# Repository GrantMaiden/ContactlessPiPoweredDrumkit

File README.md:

#  (byte)this.beat  
Welcome to the github landing page for the first prototype of the **(byte)this.beat** drumkit!

(byte)this.beat is an innovative, contactless, raspberry pi-powered drumkit being developed for  Real Time Embedded Programming (ENG5220) at the University of Glasgow.  The contactless drumkit aims to be a simple, easy-to-use interface that accommodates entry level users---being a introductory device to jam out on---as well as a device for professional musicians, conforming to sub 20ms latency requirements and high quality, 48000khz drum samples.

Please download the latest release to access the most recent stable version of the source code. Keep in mind that hardware is required to run this project!

## So what's the tempo?

* The challenge set for this course was to develop any real time embedded project, using a Raspberry Pi 3 and a £45 budget.  
* Selecting an appropriate sensor that can be used in a real-time system that is affordable, has a high sample rate, and great data resolution was challenging. After a thorough amount of market research, the [VL53L4CD](https://www.st.com/en/imaging-and-photonics-solutions/vl53l4cd.html) ranging sensor was selected as the most suitable ic for our project. Turning them into "invisible" drum modules so that you can jam out in thin air seemed a perfect task!  
* The distance values measured by the sensors every 10ms are used to calculate the velocity of any objects directly above the sensors. A detection algorithm is derived by being a combination of when the velocity changes direction, and what the previous 80ms of velocity was measured as. Thus, it is possible to use the sensor data to not only detect when a drum hit has been detected, but also at what intensity!

## Team Collaboration and Project Management

Project management was done by utilising a teams channel for collaboration. At the start of our group project, keeping in mind an agile team development environment, a Gantt chart was created in excel and hosted on our teams channel. Our team had two meetings each week throughout the semester; the first of which was primarily for project planning and updates, and the second meeting was for development and one-on-one problem solving, if necessary. Github issues were utilised as a means to give feedback as our project development continued. All Project Discussions, meeting notes, and development feasibility studies can be found at our [sharepoint](https://gla.sharepoint.com/:o:/s/ENG5228RTEP/Er4JzmCRMUZCnUjhNUSQIA8BrX5IVSQI6c456dHyLfZf0w?e=HDqj4z).  
This link is accessible by anyone with a University of Glasgow account. 
GitHub issues were used as a way to track the development of the project. The issues can be viewed from the header of this page, above the directory browser.

## Project Setup and Initialisation
### Hardware Requirements
* Assembled (byte)this.beat board
* Raspberry Pi updated with latest Raspbian image
* Speaker attached to Audio Jack
### Software Setup
* Complete project setup instructions located in the [Embedded Directory](https://github.com/GrantMaiden/ContactlessPiPoweredDrumkit/tree/main/embedded) on your local raspberry pi
* Download the latest release of the firmware, and compile the source code in the embedded directory by following the [cmake build instructions](https://github.com/GrantMaiden/ContactlessPiPoweredDrumkit/blob/main/embedded/cmake_build_instructions.txt)

After running the program, an intro LED pattern will play for roughly 5 seconds, which when complete the drumkit will be able to receive ranging data. To enable sound, swipe across all 4 upwards facing sensors. The same swipe can be used to disable sound if playing needs to be paused.

## Documentation
Our code has been updated with comments that are compatible with DoxyGen, which is a great tool to generate large amounts of sufficiently segmented documentation. To view the generated documentation, first grab the latest release, then open the index.html page located in the [embedded/docs](https://github.com/GrantMaiden/ContactlessPiPoweredDrumkit/tree/main/embedded/docs) directory. In addition to the DoxyGen resource, the source code is litered with verbose explanaitons and function headers, so keep that in mind if you are modifying the source.

## Hardware Development
In order to minimise costs associated with the (byte)this.beat project, a custom Hardware design was developed. After a cost analysis completed at the beginning of the project timeline, it was concluded that designing a custom solution, rather than purchasing independent breakout boards, would allow our contactless drumkit to have a larger scope. Thus accommodating more sensors/functionality by more easily staying within our £45 budget. The discussions pertaining to analysis and cost can be seen at our [onenote](https://gla.sharepoint.com/:o:/s/ENG5228RTEP/Er4JzmCRMUZCnUjhNUSQIA8BrX5IVSQI6c456dHyLfZf0w?e=HDqj4z).  

As always, the goal with any project is to learn as much as possible while designing, thus we decided to use this opportunity to get familiar with KiCad for schematic entry. A prototype design was completed early into the semester, giving our team plenty of tolerance on receiving the fabricated boards. The fabricated board can also easily accommodate many more traces and connections than a breadboard solution could, allowing for the design scope to increase. The schematic can be seen [here](https://github.com/GrantMaiden/ContactlessPiPoweredDrumkit/blob/main/hardware/ContactlessPiPoweredDrumkit/Schematic/byteThisBeatREVA.pdf).

The drumkit had a portion of the budget left over after the primary sensor selection, so we decided to use the rest of the funds on purchasing LEDs that would aid in giving the drummer feedback during hit detection. As seen in the block diagram below, the raspberry pi communicates with 6 distance sensors, outputs to the on-board audio jack, and outputs serialised data to the LEDs.

The LEDs that were chosen are the same type of addressable LEDs that can be found on LED strips. They are affordable, and plenty of options are available. A few design challenges had to be faced regarding the decision to use these leds, however. The LEDs use 5V logic for communication, so a level shifter had to be added to translate the rpi's 3.3V logic to 5V. Secondly, the LEDs use a strict 800khz transmission rate for each bit. Serialised bits need to be given to the LEDs over a single trace, essentially the LEDs act as specialised shift registers, only forwarding their to each succeeding LED after 24bits of data has been received. The data sheet for the LEDs, along with more information regarding the protocol, can be found [here](https://github.com/GrantMaiden/ContactlessPiPoweredDrumkit/blob/main/docs/datasheets/IN-PI55TAT(X)R(X)G(X)B_v1.5.pdf). 

Due to the strict timing requirement of the LEDs, we had to use a hardware bus to send the LED bitstream, given that bitbanging at 800khz would not be consistent, and would cause too much overhead. Initially, the PCB was designed to use the uart interface for driving the LEDs, but after getting the boards in-hand and beginning development, it was found that the uart bus could not support the baudrate required (800khz*(8bits + 1stopbit) = 7.2mhz), a hardware rework was completed to change the LED control over to the SPI bus, which could accommodate the necessary frequency. The rework instructions can be found in the hardware directory.

For more information regarding the manufacturing of the (byte)this.beat board, please refer to the [hardware directory](https://github.com/GrantMaiden/ContactlessPiPoweredDrumkit/tree/main/hardware/ContactlessPiPoweredDrumkit), which includes a BOM for manufacture. The board file can also be seen in this directory. Layout was completed using KiCad, with a two-layer PCB being designed. After meeting with the EE technicians at the University of Glasgow, we found that they were unable to fabricate our design, so an overseas location was chosen for fab and assembly.

## Software 

The embedded code, being the main focus of our project, was approached with several goals for implementation:
* Real Time Coding - code is event driven and utilises hardware inputs or timers to strictly control code behavior
* Event Handling - real time events are coded with clearly defined callbacks and other async operations
* Class Encapsulation - code is written within separate classes that have clear responsibilities, obey the Liskov Substitution Principle, and are segregated, with dependency inversion
* Documentation - Verbose function headers and additional documentation generated with Doxygen to supply the user information
* Header File Constants - many constants included to aid in program control and easily modify behavior

Below, please see a diagram regarding how the major classes interact with each other within our application.

The controller class is initialised by the Main function, which on program boot creates the initial controller class. When the controller class is initialised, it will bring up the other portions of the program, which configures any necessary peripherals, and performs the bring-up procedure of the ranging sensors. This initialisation also configures asynchronous processes that use callback processes to create real-time operation of our system. The LED class uses a timer, and updates all LEDs every 2.5ms. The VL53L4CD class leaves an abstract function that is defined within the Controller class. When a hardware interrupt occurs, the VL53L4CD class will enact a callback via the virtual function.

### Bus Protocols
I2C was used as the communication protocol for each sensor. All sensors share the same bus, but are initialised with the same address. An initialization procedure had to be crafted to disable all sensors on program start, then bring-up each sensor sequentially, reprogramming the I2C bus address for the sensor, and configuring it for our high sample rate requirements.

Note: From VL53L4CD Datasheet

The SPI protocol uses custom bitshift operations to drive 6*24bits of RGB data to our addressable LEDs. The GPIO controller class handles the sending of the SPI data.
### Digital Signal Processing
The outgoing data from the ranging sensors is inherently quite noisy, and lots of artifacts exist especially once you begin to interact with them. In order to have reliable air drumming behavior, it was necessary to come up with multiple algorithms that filter the data in various ways. Keeping in mind the real-time requirements of our system, a lengthy finite reponse filter could not be used due to adding to much delay to the total system overhead. To minimise response delays, filtering was controlled using the following methods, configurable inside the controller.h header file:
* HIT_DETECT_NOISE_CHECKING   -- Enable Noise Checking/Filtering
* HIT_DETECT_NUM_SAMPLES_MIN   -- Minimum number of samples necessary for detection
* DRUM_INTERVAL_TIMEOUT_MS  -- Timeout between detection events. Caps maximum drum rate per drum
* HIT_DETECT_INSTANEOUS_VELOCITY_LIMIT  --  Velocity artificats occur frequently. If one of the detection samples' velocity is above this limit, then the drum detect is cancelled
* HIT_DETECT_AVG_VELOCITY_CEILING -- An average velocity is taken of all previous detection samples. If this average is above this threshold, then the drum detect event is negated
* HIT_DETECT_MIN_SEQUENTIAL_VELOCITY_SAMPLES  --  Minimum number of previous velocity samples below the HIT_DETECT_AVG_VELOCITY_CEILING required for a hit detect

Whenever a sensor receives data, via a virtual callback the data is sent to the controller class for processing. The controller class will take the most recent data, store the last 16 distance values into an array, and calculate the most recent velocity by taking the last sample minus the most recent sample. When the velocity calculation occurs, the velocity data is ran through a simple running average filter, via the calculation: averageVelocity = averageVelocity + (recentVelocity - averageVelocity) / VELOCITY_FACTOR_AVG. The VELOCITY_FACTOR_AVG is a constant modifiable in the controller.h header file.
A running average filter allows for a single sample overhead during averaging, and converges completely to the real average within the VELOCITY_FACTOR_AVERAGE number of samples.
As a brief example of the challenges seen during data collection and processing, refer to the below image. This image shows the Average Velocity, Recent Velocity, and current distance of each sample, in 10ms increments. 
 
## Phone Application
 
Originally, ambitious project planning had our team plan on utilising a phone application to interact with the physical drumkit, using bluetooth to handshake, modify drumkit selections, and use the phone as a speaker. We did have the opportunity to develop a prototype phone app early on in the semester. However, due to team bandwidth limitations, we were unable to see the bluetooth connectivity and phone app through to completion. 
 
It should be noted that we also discovered though substantial literature review that bluetooth bandwidth is relatively inconsistent, and even the bluetooth low latency has minimum latency intervals of about 70ms. We concluded that using bluetooth as a realtime interface would be a nightmare, and it would be best to at least keep to a physical connection regarding the sound output. We still think that a phone app would be a great way to interact with the drumkit settings, volume, etc., any we plan to continue to consider implementing one in the future.

## Unit Testing Framework
A custom unit testing framework was designed to accommodate the needs of our team collaborative efforts. When the application launches, the first code that is ran is a search to see if any input arguments are supplied. The input arguments are the inputs to our custom unit testing framework; it was deemed necessary to have a more advanced testing methodology in place as the many different blocks of our project required separate entry points depending on use case. In example, a unit test was designed to benchmark and initialise the LEDs. After the unit test was completed, the functions designed during test were integrated into the rest of the project. This design methodology was enacted in all facets of our software development. 

A list of all unit tests, their associated functions, and more specific usage instructions can be found [here](https://github.com/GrantMaiden/ContactlessPiPoweredDrumkit/blob/main/embedded/unit_tests.txt).

## Challenges and Future Improvements
Development using the raspberry pi proved to be full of challenges. Some of our team has had extensive experience with varying microcontrollers as a professional embedded engineer, and they concluded that the lack of substantial official documentation greatly complicated development. 
Here is a list of (just a few!) of the notable challenges that arose during development:
* Audio permissions -- The pigpio library requires sudo permissions, however the asla audio driver is not configured correctly to run under super user. The solution was challenging to discover, but is highlighted in the markup in our embedded directory.
* SPI bus frequency -- The embedded core clock used by the PI is not consistent. Our addressable LEDs requires fixed timing to work correctly, however the SPI clock is affected by other bus activity, USB traffic, and high load wifi connections. Essenstially, the LEDs will flicker or flash random colors when the SPI frequency deviates. As far as we know, there is no solution to this problem, but it shows that the raspberry pi is full of undocumented surprises, and is not capable of specific timing control under some circumstances.
* Some low level c libraries such as pigpio have functions to modify embedded bus behaviour, but really these values are controlled by the us and it is necessary to modify the /boot/firmware/config.txt to change things such as the I2C clock speed.
* The SPI cs gpio's can not be used as GPIO's during spi, even if SPI0 is being used, and SPI1 CS is trying to be configured as an input, even when all documentation says otherwise. This required a rework!

Some future improvements for the drumkit are planned for the next revision of the project.

* Move away from the high power, large raspberry pi to a smaller mcu. Originally one of the goals of our project was to make a device small and portable; a criteria that our device doesn't quite meet.
* Implement bluetooth communication that will interact with a peripheral phone app for control and feedback.
* Respin the board to correct hardware reworks required to accomodate SPI CS GPIO bottlenecking, and switching to the SPI from UART for LED control.
* Improve hit detection by exploring other filtering methods, and perhaps different sensors.

## Authors

* Grant Maiden  
* Peter O'Hanlon  
* Ethan Travers  
* Lucas Zehner

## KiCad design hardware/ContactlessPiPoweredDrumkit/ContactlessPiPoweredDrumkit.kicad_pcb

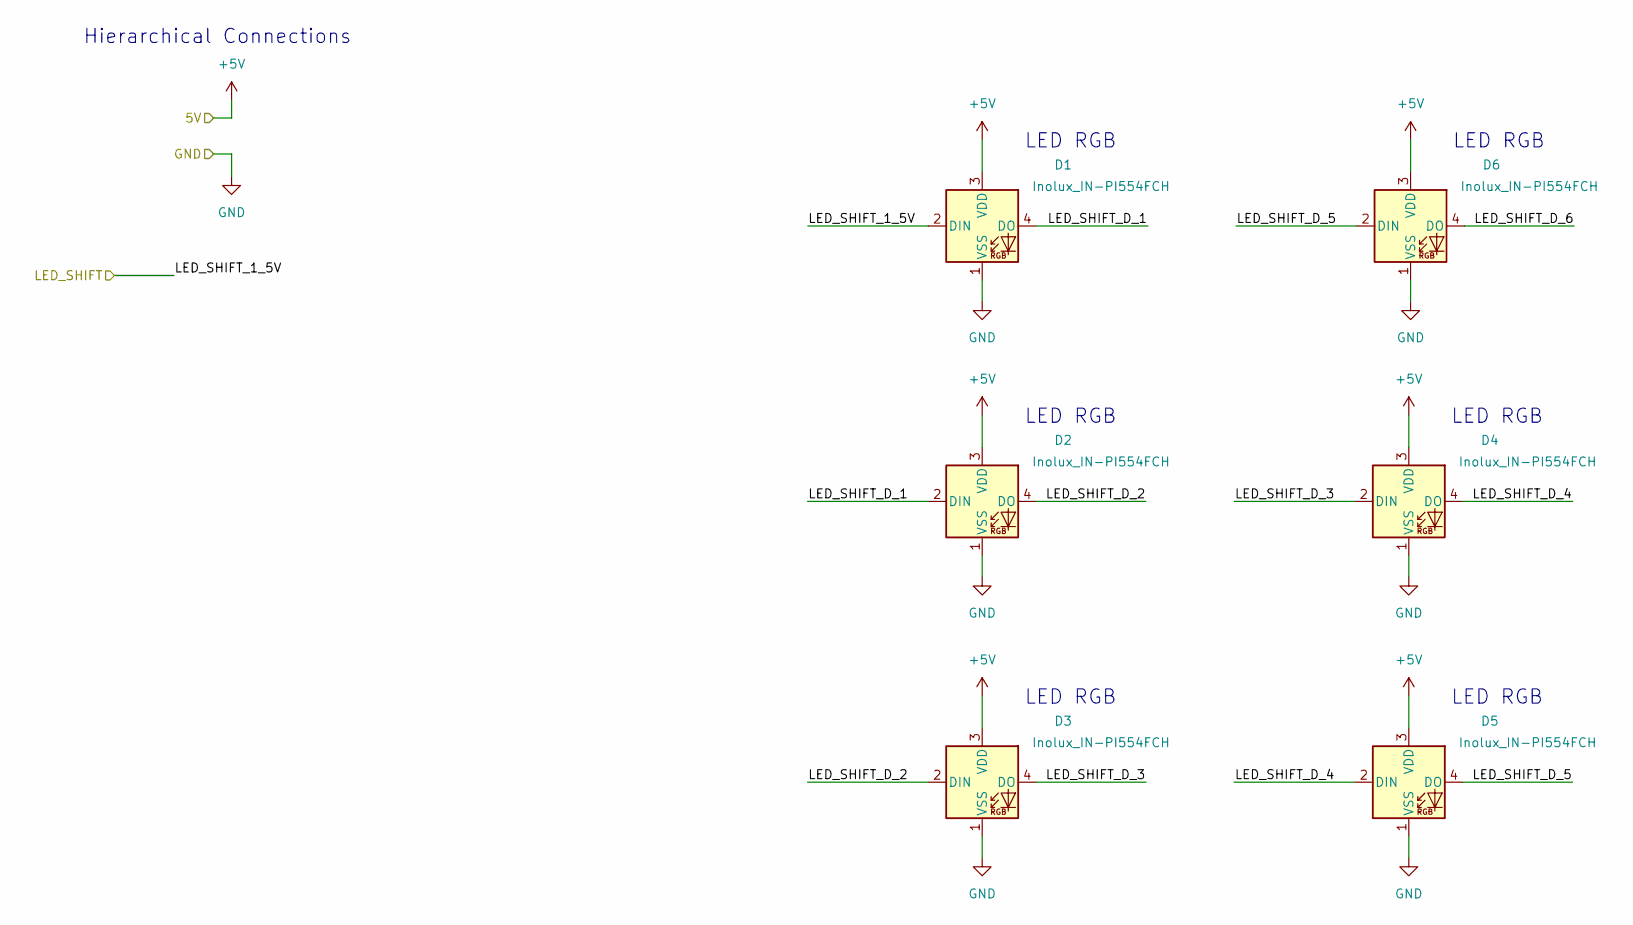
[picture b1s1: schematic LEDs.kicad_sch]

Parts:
D1, D2, D3, D4, D5, D6: Inolux_IN-PI554FCH; LED_Inolux_IN-PI554FCH_PLCC4_5.0x5.0mm_P3.2mm

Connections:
+5V: D1.3 (VDD), D2.3 (VDD), D3.3 (VDD), D4.3 (VDD), D5.3 (VDD), D6.3 (VDD); also elsewhere on the board
/LEDs/LED_SHIFT_1_5V: D1.2 (DIN); also elsewhere on the board
/LEDs/LED_SHIFT_D_1: D1.4 (DO), D2.2 (DIN)
/LEDs/LED_SHIFT_D_2: D2.4 (DO), D3.2 (DIN)
/LEDs/LED_SHIFT_D_3: D3.4 (DO), D4.2 (DIN)
/LEDs/LED_SHIFT_D_4: D4.4 (DO), D5.2 (DIN)
/LEDs/LED_SHIFT_D_5: D5.4 (DO), D6.2 (DIN)
/LEDs/LED_SHIFT_D_6: D6.4 (DO)
GND: D1.1 (VSS), D2.1 (VSS), D3.1 (VSS), D4.1 (VSS), D5.1 (VSS), D6.1 (VSS); also elsewhere on the board

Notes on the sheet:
LED RGB
Hierarchical Connections

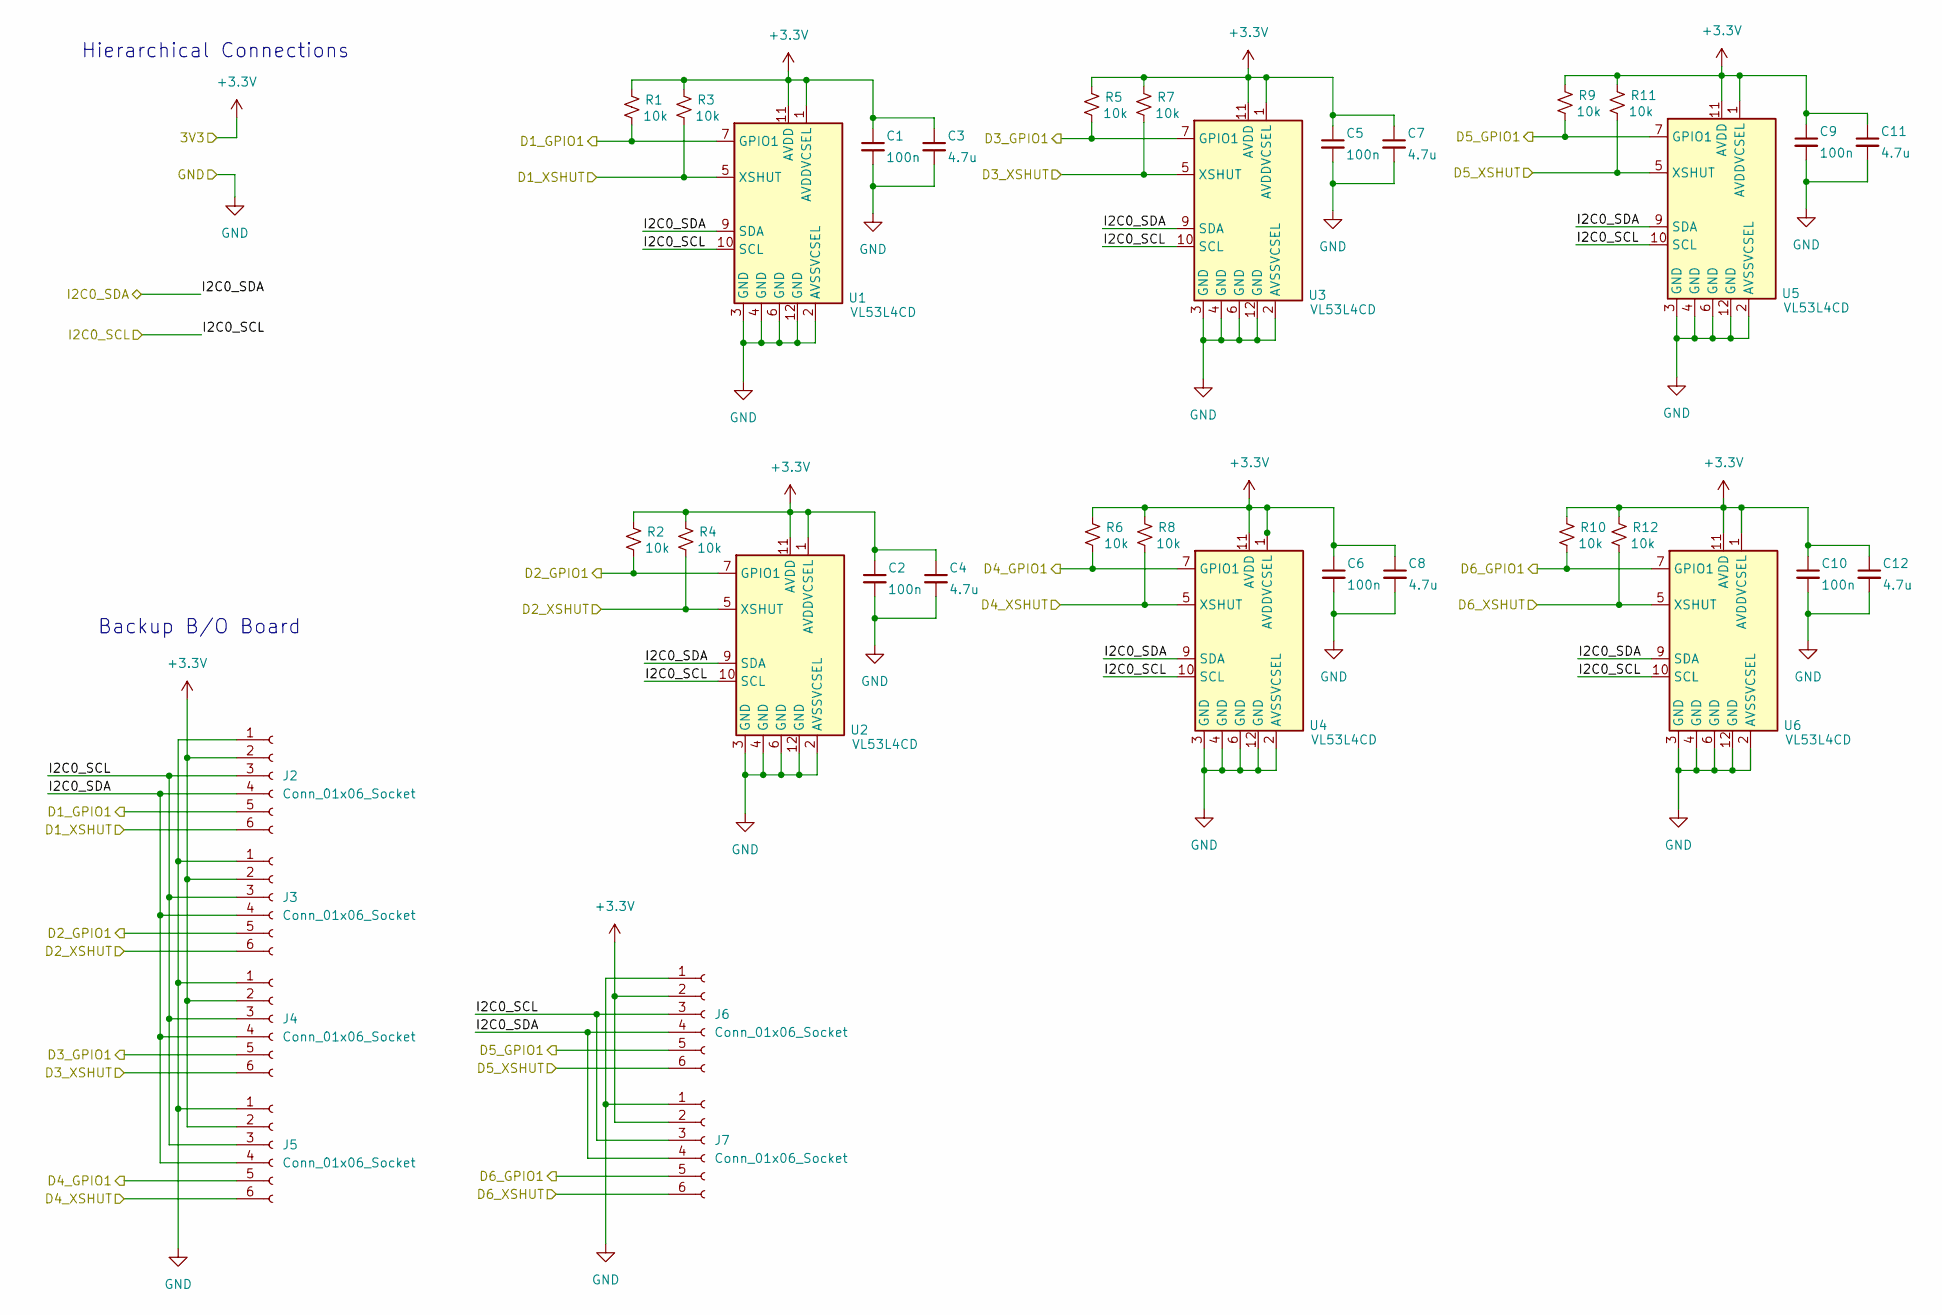
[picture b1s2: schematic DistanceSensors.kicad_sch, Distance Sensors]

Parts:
C1, C2, C5, C6, C9, C10: 100n; C_0603_1608Metric
C3, C4, C7, C8, C11, C12: 4.7u; C_0603_1608Metric
J2, J3, J4, J5, J6, J7: Conn_01x06_Socket; PinSocket_1x06_P2.54mm_Vertical
R1, R2, R3, R4, R5, R6, R7, R8, R9, R10, R11, R12: 10k; R_0603_1608Metric
U1, U2, U3, U4, U5, U6: VL53L4CD; ST_VL53L1x

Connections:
+3.3V: C1.1, C2.1, C3.1, C4.1, C5.1, C6.1, C7.1, C8.1, C9.1, C10.1, C11.1, C12.1, J2.2, J3.2, J4.2, J5.2, J6.2, J7.2, R1.1, R2.1, R3.1, R4.1, R5.1, R6.1, R7.1, R8.1, R9.1, R10.1, R11.1, R12.1, U1.1 (AVDDVCSEL), U1.11 (AVDD), U2.1 (AVDDVCSEL), U2.11 (AVDD), U3.1 (AVDDVCSEL), U3.11 (AVDD), U4.1 (AVDDVCSEL), U4.11 (AVDD), U5.1 (AVDDVCSEL), U5.11 (AVDD), U6.1 (AVDDVCSEL), U6.11 (AVDD); also elsewhere on the board
/Distance Sensors/D1_GPIO1: J2.5, R1.2, U1.7 (GPIO1); also elsewhere on the board
/Distance Sensors/D1_XSHUT: J2.6, R3.2, U1.5 (XSHUT); also elsewhere on the board
/Distance Sensors/D2_GPIO1: J3.5, R2.2, U2.7 (GPIO1); also elsewhere on the board
/Distance Sensors/D2_XSHUT: J3.6, R4.2, U2.5 (XSHUT); also elsewhere on the board
/Distance Sensors/D3_GPIO1: J4.5, R5.2, U3.7 (GPIO1); also elsewhere on the board
/Distance Sensors/D3_XSHUT: J4.6, R7.2, U3.5 (XSHUT); also elsewhere on the board
/Distance Sensors/D4_GPIO1: J5.5, R6.2, U4.7 (GPIO1); also elsewhere on the board
/Distance Sensors/D4_XSHUT: J5.6, R8.2, U4.5 (XSHUT); also elsewhere on the board
/Distance Sensors/D5_GPIO1: J6.5, R9.2, U5.7 (GPIO1); also elsewhere on the board
/Distance Sensors/D5_XSHUT: J6.6, R11.2, U5.5 (XSHUT); also elsewhere on the board
/Distance Sensors/D6_GPIO1: J7.5, R10.2, U6.7 (GPIO1); also elsewhere on the board
/Distance Sensors/D6_XSHUT: J7.6, R12.2, U6.5 (XSHUT); also elsewhere on the board
/I2C0_SCL: J2.4, J3.4, J4.4, J5.4, J6.4, J7.4, U1.9 (SDA), U2.9 (SDA), U3.9 (SDA), U4.9 (SDA), U5.9 (SDA), U6.9 (SDA); also elsewhere on the board
/I2C0_SDA: J2.3, J3.3, J4.3, J5.3, J6.3, J7.3, U1.10 (SCL), U2.10 (SCL), U3.10 (SCL), U4.10 (SCL), U5.10 (SCL), U6.10 (SCL); also elsewhere on the board
GND: C1.2, C2.2, C3.2, C4.2, C5.2, C6.2, C7.2, C8.2, C9.2, C10.2, C11.2, C12.2, J2.1, J3.1, J4.1, J5.1, J6.1, J7.1, U1.2 (AVSSVCSEL), U1.3 (GND), U1.4 (GND), U1.6 (GND), U1.12 (GND), U2.2 (AVSSVCSEL), U2.3 (GND), U2.4 (GND), U2.6 (GND), U2.12 (GND), U3.2 (AVSSVCSEL), U3.3 (GND), U3.4 (GND), U3.6 (GND), U3.12 (GND), U4.2 (AVSSVCSEL), U4.3 (GND), U4.4 (GND), U4.6 (GND), U4.12 (GND), U5.2 (AVSSVCSEL), U5.3 (GND), U5.4 (GND), U5.6 (GND), U5.12 (GND), U6.2 (AVSSVCSEL), U6.3 (GND), U6.4 (GND), U6.6 (GND), U6.12 (GND); also elsewhere on the board

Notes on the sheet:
Backup B/O Board
Hierarchical Connections

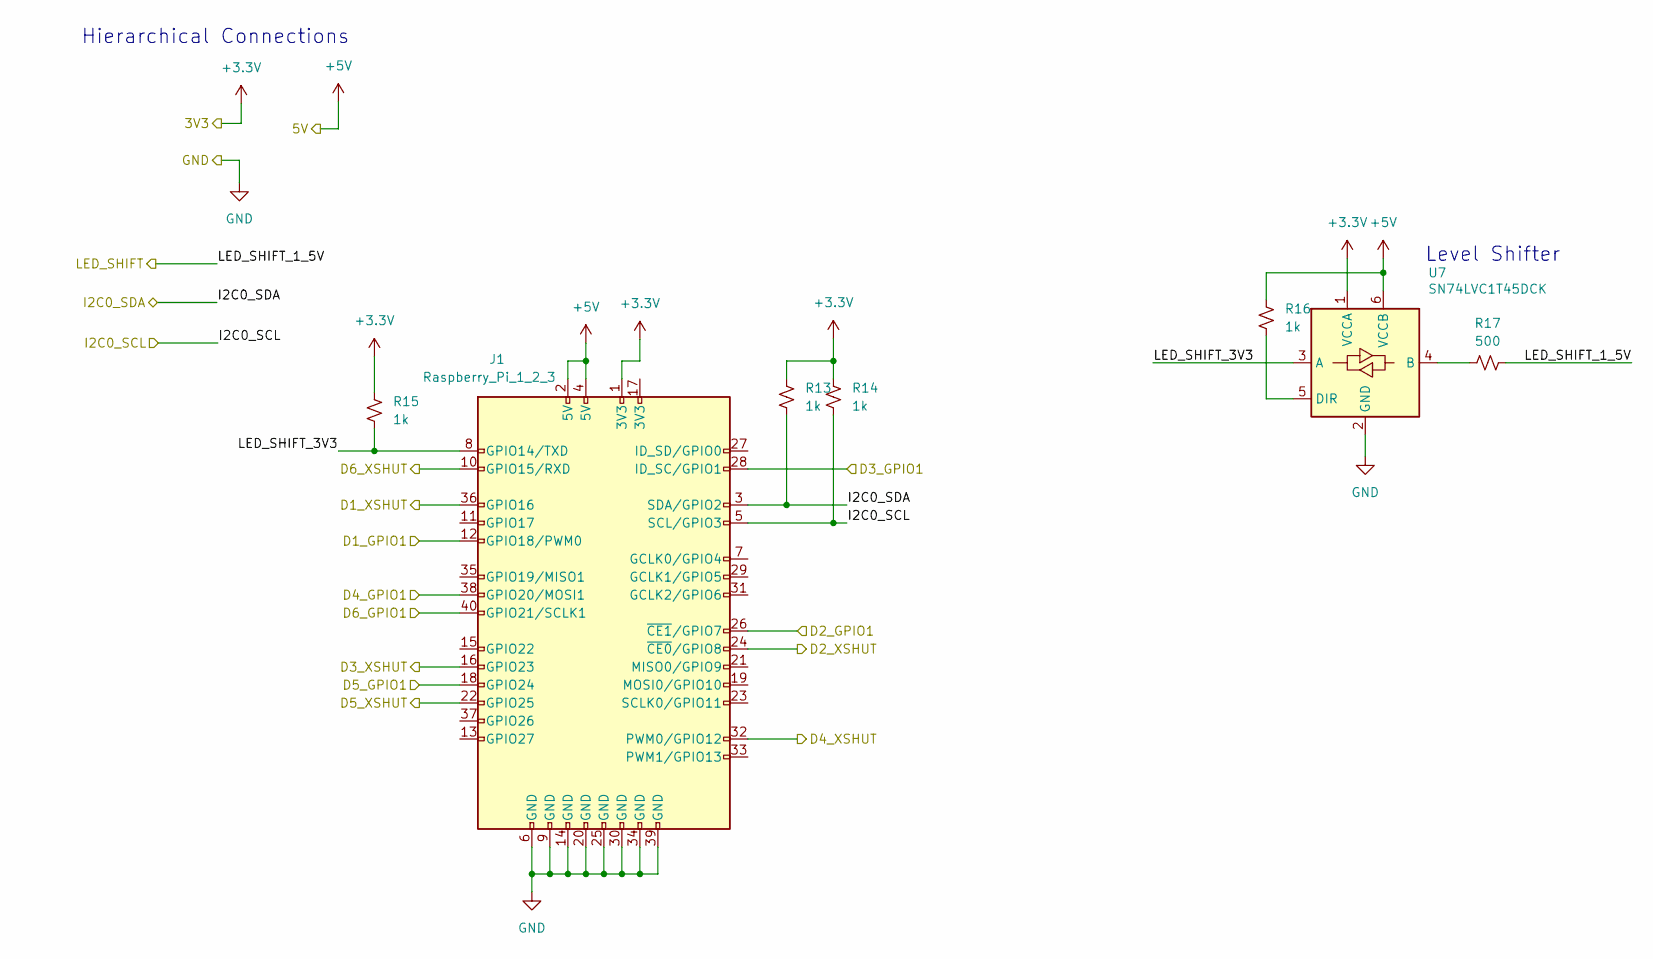
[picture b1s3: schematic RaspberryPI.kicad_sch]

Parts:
J1: Raspberry_Pi_1_2_3; PinSocket_2x20_P2.54mm_Vertical
R13, R14, R15, R16: 1k; R_0603_1608Metric
R17: 500; R_0603_1608Metric
U7: SN74LVC1T45DCK; SOT-363_SC-70-6

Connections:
+3.3V: J1.1 (3V3), R13.1, R14.1, R15.1, U7.1 (VCCA); also elsewhere on the board
+5V: J1.2 (5V), J1.4 (5V), R16.1, U7.6 (VCCB); also elsewhere on the board
/Distance Sensors/D1_GPIO1: J1.12 (GPIO18/PWM0); also elsewhere on the board
/Distance Sensors/D1_XSHUT: J1.36 (GPIO16); also elsewhere on the board
/Distance Sensors/D2_GPIO1: J1.26 (~CE1/GPIO7); also elsewhere on the board
/Distance Sensors/D2_XSHUT: J1.24 (~CE0/GPIO8); also elsewhere on the board
/Distance Sensors/D3_GPIO1: J1.28 (ID_SC/GPIO1); also elsewhere on the board
/Distance Sensors/D3_XSHUT: J1.16 (GPIO23); also elsewhere on the board
/Distance Sensors/D4_GPIO1: J1.38 (GPIO20/MOSI1); also elsewhere on the board
/Distance Sensors/D4_XSHUT: J1.32 (PWM0/GPIO12); also elsewhere on the board
/Distance Sensors/D5_GPIO1: J1.18 (GPIO24); also elsewhere on the board
/Distance Sensors/D5_XSHUT: J1.22 (GPIO25); also elsewhere on the board
/Distance Sensors/D6_GPIO1: J1.40 (GPIO21/SCLK1); also elsewhere on the board
/Distance Sensors/D6_XSHUT: J1.10 (GPIO15/RXD); also elsewhere on the board
/I2C0_SCL: J1.3 (SDA/GPIO2), R13.2; also elsewhere on the board
/I2C0_SDA: J1.5 (SCL/GPIO3), R14.2; also elsewhere on the board
/LEDs/LED_SHIFT_1_5V: R17.2; also elsewhere on the board
/Raspberry PI/LED_SHIFT_3V3: J1.8 (GPIO14/TXD), R15.2, U7.3 (A)
GND: J1.6 (GND), J1.9 (GND), J1.14 (GND), J1.20 (GND), J1.25 (GND), J1.30 (GND), J1.34 (GND), J1.39 (GND), U7.2 (GND); also elsewhere on the board
unnamed: R17.1, U7.4 (B)
unnamed: R16.2, U7.5 (DIR)

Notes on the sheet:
Hierarchical Connections
Level Shifter

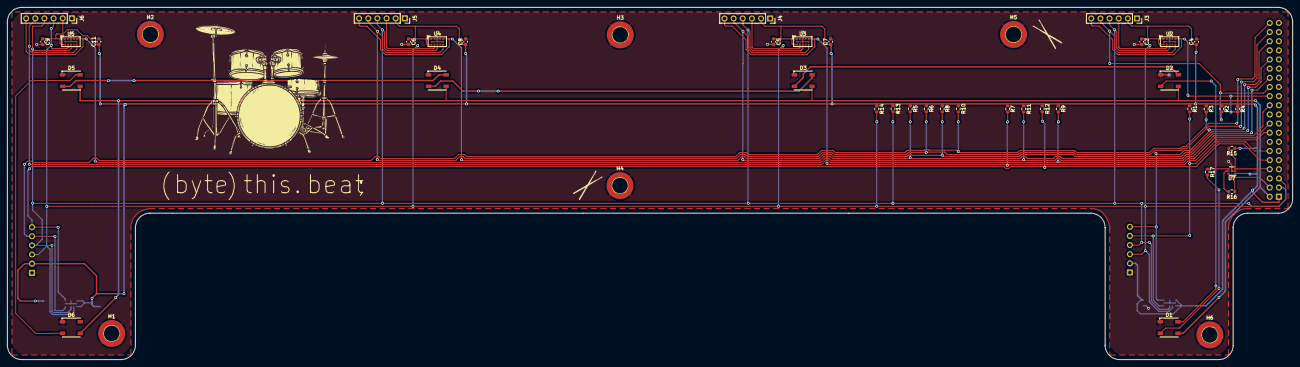
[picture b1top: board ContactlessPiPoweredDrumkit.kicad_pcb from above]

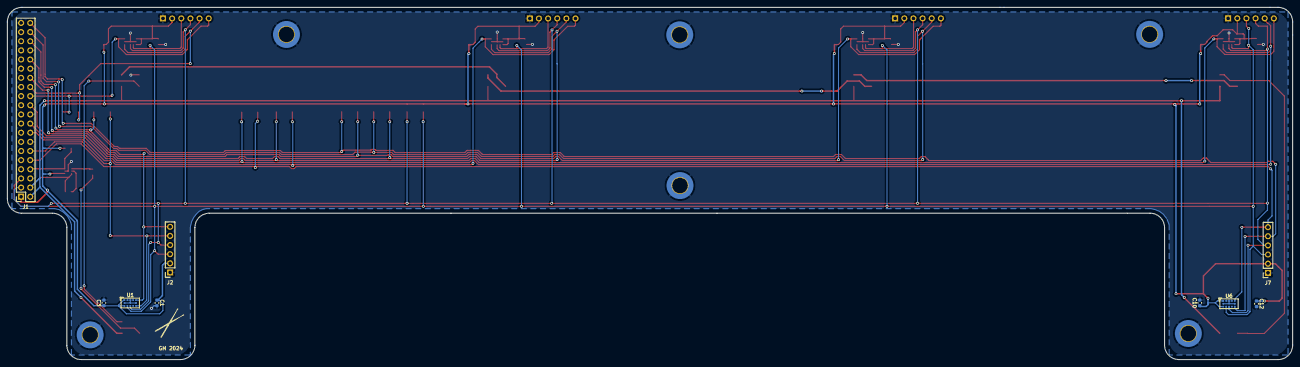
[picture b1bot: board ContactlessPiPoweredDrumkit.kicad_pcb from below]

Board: 2 copper layers, 356.9 x 97.8 mm, 55 parts (9 on the bottom side), 26 nets.

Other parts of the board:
H1, H2, H3, H4, H5, H6: MountingHole_Pad; MountingHole_4.3mm_M4_DIN965_Pad_TopBottom

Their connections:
GND: H1.1, H2.1, H3.1, H4.1, H5.1, H6.1; also elsewhere on the board

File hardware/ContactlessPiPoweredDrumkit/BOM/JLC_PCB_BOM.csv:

Designator,Quantity,Value,Footprint,LSCS Part #
"C2, C5, C6, C9",4,100n,603,C14663 
"C4, C7, C8, C11",4,4.7u,603,C19666 
"R1, R2, R3, R4, R5, R6, R7, R8, R9, R10, R11, R12",12,10k,603,C25804 
"R13, R14, R15, R16",4,1k,603,C21190 
R17,1,470,603,C23179 
"U2, U3, U4, U5",4,VL53L4CD,Sensor_Distance:ST_VL53L1x,C3178291
U7,1,SN74LVC1T45DCK,SC-70-6,C9382

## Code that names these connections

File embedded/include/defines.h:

/****************************** Module Header ******************************\
Module Name:    defines.h
Project:        btb
Author:         Grant Maiden
Description:    contains user constants, global enums, and structs
\***************************************************************************/
#ifndef DEFINES_H
#define DEFINES_H

// Test defines
#define GPIO_TEST_LENGTH_SEC                10
#define TOTAL_INSTRUMENTS_SOUND_TEST2       3

// Misc
#define DISTANCE_SENSOR_INTERRUPT_TIMEOUT   20
#define BTB_TIMER_1_INTERVAL_NS             2.5*1000000

// Gpio Controller Defines
#define WAIT_10MS       1551000
#define WAIT_5MS        775000
#define WAIT_2MS        310200
#define WAIT_1MS        155100
#define WAIT_100US      15510
#define WAIT_245NS      38
#define WAIT_190NS      29
#define WAIT_50NS       8

// Gpio Defines
#define PI_LOW          0
#define PI_HIGH         1
#define GPIO4           4

#define LED_SHIFT_3V3   14
#define D1_GPIO1        18
#define D1_XSHUT        16
#define D2_GPIO1        22
#define D2_XSHUT        8
#define D3_GPIO1        1
#define D3_XSHUT        23
#define D4_GPIO1        20
#define D4_XSHUT        12
#define D5_GPIO1        24
#define D5_XSHUT        25
#define D6_GPIO1        21
#define D6_XSHUT        15

typedef enum
{
    SENSOR1,
    SENSOR2,
    SENSOR3,
    SENSOR4,
    SENSOR5,
    SENSOR6
}sensorID;

// Structs

/**
 * sensorValues structure contains status and distance value of a sensor
 **/
typedef struct
{
    uint8_t rangeStatus; // range status 0 means data ready.
    uint16_t currentDistance_mm;
    uint16_t lastDistance_mm;
    int currentVelocity;
    int averageVelocity;
}sensorValues;

#endif

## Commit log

2024-01-21 Add Datasheets
2024-01-21 Initial Commit Schematic
2024-01-21 Add Datasheet for Distance Sensor
2024-01-21 Add Hierarchical Connections and Distance Sensors
2024-01-21 Bom Updates
2024-01-21 Update Hierarchy Page
2024-01-22 Phone App Initial commit
2024-01-23 Update Launcher Icon and Splash Screen
2024-01-23 Update MainActivity.kt
    Add Intro Drum Kit sounds
2024-01-23 Add Drumkit to Main Screen
2024-01-24 Update README.md
    Added instagram link
2024-02-05 Complete PCB Layout
    Completed PCB layout
    Custom Artwork
    Generate Gerbers
2024-02-05 Commit missed items
    Missed a few items
2024-02-05 Create Schematic PDF
    Created Schematic PDF
2024-02-05 Create BOM
    Create BOM
    Modify Directory Structure
2024-02-05 Reviewed PCB DRC
    Reduced constraint size from .3mm to .25mm
    Move pullup resistors slightly
2024-02-06 Updated Manufacturing Zip
    Zip updates, change drill constraints
2024-02-06 Correct Silkscreen/Update SCH
    correct silkscreen and update schematic
2024-02-08 Board Build modifications
    Move traces slightly further from board edge.
    Create seperate BOM and placement file for JCLPCB
2024-02-15 Upload Linux Kernal for Distance Sensor
2024-02-17 Embedded Project Initialization
    Configure Codeblocks
    Include I2C example
    Format Directory
    Update Readme Markdown
2024-02-17 Correct some descriptors
2024-02-18 Update project for doxyGen format
2024-02-18 Add i2c enable steps to readme
    modify readme to help team members setup their pi's correctly
2024-02-22 Add GPIO library
    Update main function to have a GPIO test, and give an example of how to shutdown distance sensors, leaving one enabled.
2024-02-22 Update defines.h
    Add LED_SHIFT_3V3
2024-02-24 Add SPI led control
    Add LED control over spi
    Add test commands
    Add LED library and color defines
2024-02-25 SPI Improvements
    Simplify Changes colors to one function call
    Add defines for more colors
    Remove antiquated files and directories
2024-02-26 Change Spi defines
    Spi board rework does not need repeated SPI.
2024-02-26 Change SPI back to 200us reset
2024-02-26 Add GPIO interrupts for Distance Sensors
    Add GPIO interrupts.
    Interrupt function callback needs to be moved to ranging.cpp @LucasZehner
2024-02-27 Add files via upload
    state machine and unit test function added
2024-02-28 Change SPI timing slightly
2024-02-28 Setup for the ranging sensor unit test
    Added:
    Sensor GpIO logic selection, ChangeAddress, StartRanging
2024-02-28 Sensor initialisation
    Successfully initialised sensors 2-5.
    New 'Dev_t' global object for each sensor.
2024-02-28 LED Control changes
    extra initialisation cases
2024-02-28 Updated Initialise LEDs
    fixed timing issues with final states of state-machine
2024-02-29 Clean directory, Add Cmake files
    Clean directory
    Add Cmake Files for cmake based building
    Add cmake_build_instructions.txt
    Add unit_tests.txt
2024-02-29 Create Cmakelists for cmake builds
2024-02-29 Update readme.md
    Add newline characters to aid in spacing+readability
2024-03-01 Removed unnecessary files
    bin, obj, layout, depend
2024-03-02 Add Thread and Timer Callbacks
    Add Thread and Timer Callbacks.
    Add interruptTest unitTest.
    Purge btb_main.cpp/h of distance sensor functions
2024-03-02 fix markdown blanking whitespace characters.
2024-03-02 Add newline double space to pigpio debug sections
2024-03-03 controller updates and Doxygen
    Create controller State machine
    Add functions for hit detection, velocity calculations, and updating sensorValues
    Add defines, structs, and enums to defines.h to help move sensor data between modules
    Add Doxygen file
2024-03-04 Upload Sounds
    Record sounds with audacity
2024-03-04 rename sounds folder
2024-03-04 Init
    Imported various CAD models, initial sketch (very basic)
2024-03-04 Ranging functions
    Attempted (and failed) simultaneous ranging test.
    Added interrupt-called single-sensor range poll function.
2024-03-05 functions added to clean up code + state machine started for main function LED feedback
2024-03-05 modify logic in controllerUpdatSensorValue
2024-03-05 some fixes to previous commit
2024-03-06 Sound Functional
    Incorporate "miniAudio" library into our project.
    More setup required, refer to readme.md
    Fix some warnings
    Add unit tests for soundTest1, soundTest2, soundTest3
    Update CMake to work with miniAudio library
    Delete unused test directory and examples directory.
2024-03-06 Fix some merging issues
2024-03-06 Ranging test functional.
    Need to port to all sensors simultaneously
2024-03-06 Add interrupt based Polling test
2024-03-08 Board Rework Changes
    Add Sections to Readme
    Add Acceleration print out
    Tweak Hit Detection Algorithm
2024-03-08 Drum Detect improvements
    Add Noise filtering to Drum detection.
    Many different Parameters available for adjustment in controller.h
2024-03-09 Created More Hit Detection Filters
    Additional algorithms
    Monitoring Number of average velocity vectors.
    Helps get rid of hand-over-sensor false detections
2024-03-09 updated LED Branch
2024-03-10 WIP Setup Led State Machine
    Initial setup for a proper LED state machine. There is little in here as I am hungry and need to eat. More to come
2024-03-11 Modify Entire Project to use classes
2024-03-11 Add Sounds to project
    soundTest3 is now defined.
    Sounds are enabled in project.
    Logic has been added to attach sounds to drums
2024-03-13 Update README.md
    Make it look nice
2024-03-13 Update README.md
    Typos
2024-03-13 Update readme.md
    Formatting
2024-03-13 LED StateMachine Progress Update
    Implementing LED state machine and working on helper functions.
2024-03-13 LED State Machine Update
    LED state machine has been updated with all necessary functions and logic to operate nominally. (needs to be tested after merge)
2024-03-13 Fixing Initial Merge Issues
    Main merge issues have arisen from the implementation of classes. Most of the errors have been fixed, ledControl object not being passed to controller.cpp is the main issue atm.
    Gtg home am hungry :P
2024-03-15 LED State Machine Updates
    Updates on LED SM
2024-03-16 LEDs Now Fully Functional
    Issue on my side where the LEDs will flicker when: Typing, moving mouse, printing to console. There is probably more as well. This only happens while the code runs. Additionally, sensor average veloc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
2024-03-17 Delete embedded/sounds directory
    Cleaning Up
2024-03-17 Delete embedded/btb_proj.depend
    Cleaning Up
2024-03-17 Delete embedded/btb_proj.layout
    Cleaning Up
2024-03-17 Delete embedded/bin/Debug directory
    Cleaning Up
2024-03-17 Delete embedded/obj/Debug/src directory
    Cleaning Up
2024-03-17 Re-Added Sounds
    Accidentally Removed Earlier
2024-03-20 Latest update
    Added place for fan, LED holes
2024-03-20 LED New Dynamic Range
    Added new logic for led operation as well has 5 light levels depending on hit strength. Hit strength thresholds have been moved from the controller.h to defines.h so that both classes may access them.
    sendSound function also updated to accomodate for the epic upcoming uncharted dynamic sounds
2024-03-20 Drumkit sounds
    Improved drumkit sounds added to achieve previously uncharted dynamic range.
2024-03-20 Fixes in sound.h file to initialise PI KIT
2024-03-20 updated controller.cpp to play sounds
2024-03-20 LEDs + More Sound
    Implemented the professional sounds made by Peter
2024-04-15 LED Cleanup
    Moved Defines to h file
2024-04-15 Added LED Unit Tests to txt
2024-04-16 Undo Merge that broke entire project
2024-04-16 Modify STM32 library into classes. Add virtual callbacks
2024-04-16 Fixed LED Build Issues
2024-04-16 Update classes
2024-04-16 Add doxygen docs
